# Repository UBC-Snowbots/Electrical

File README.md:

# UBC Rover Electrical Subteam Repository

Work is organized year by year (For now?)

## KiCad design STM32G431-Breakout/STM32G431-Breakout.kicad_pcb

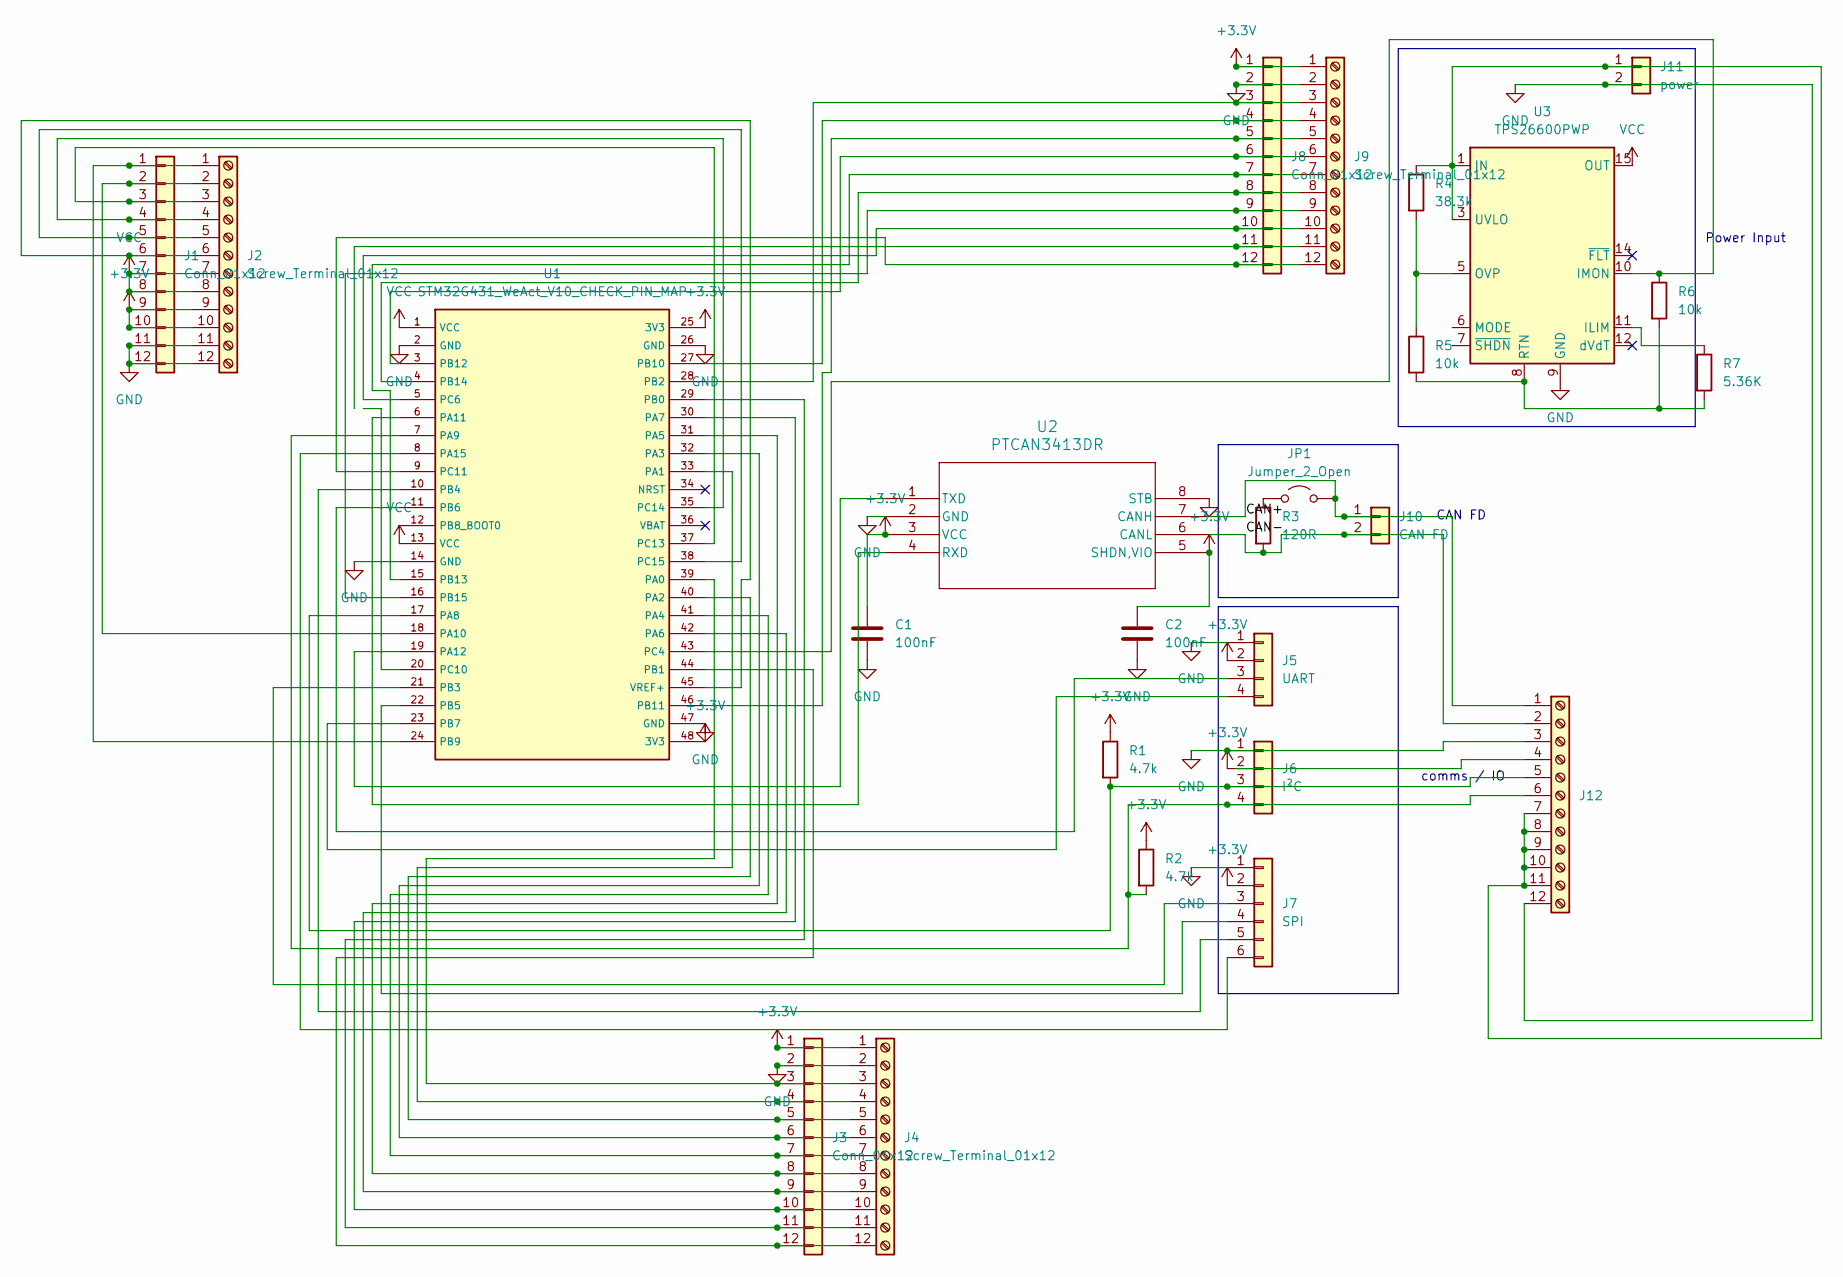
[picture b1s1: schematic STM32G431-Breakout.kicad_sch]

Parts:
C1, C2: 100nF; C_0603_1608Metric
J1, J3, J8: Conn_01x12; PinSocket_1x12_P2.54mm_Vertical
J2, J4, J9, J12: Screw_Terminal_01x12; TerminalBlock_MaiXu_MX126-5.0-12P_1x12_P5.00mm
J5: UART; JST_PH_S4B-PH-K_1x04_P2.00mm_Horizontal
J6: I²C; JST_PH_S4B-PH-K_1x04_P2.00mm_Horizontal
J7: SPI; JST_PH_S6B-PH-K_1x06_P2.00mm_Horizontal
J10: CAN FD; JST_PH_S2B-PH-K_1x02_P2.00mm_Horizontal
J11: power; JST_PH_S2B-PH-K_1x02_P2.00mm_Horizontal
JP1: Jumper_2_Open; PinHeader_1x02_P2.54mm_Vertical
R1, R2: 4.7k; R_0603_1608Metric
R3: 120R; R_0603_1608Metric
R4: 38.3k; R_0603_1608Metric
R5, R6: 10k; R_0603_1608Metric
R7: 5.36K; R_0603_1608Metric
U1: STM32G431_WeAct_V10_CHECK_PIN_MAP; stm32g431
U2: PTCAN3413DR; SOIC8_D_TEX
U3: TPS26600PWP; HTSSOP-16-1EP_4.4x5mm_P0.65mm_EP3.4x5mm_Mask2.66x2.46mm_The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

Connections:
+3.3V: C1.1, C2.1, J1.9, J1.10, J2.9, J2.10, J3.1, J4.1, J5.2, J6.2, J7.2, J8.1, J9.1, R1.1, R2.1, U1.25 (3V3), U1.48 (3V3), U2.3 (VCC), U2.5 (SHDN,VIO)
/CAN+: J10.1, J12.1, JP1.2 (B), U2.7 (CANH)
/CAN-: J10.2, J12.2, R3.2, U2.6 (CANL)
GND: C1.2, C2.2, J1.11, J1.12, J2.11, J2.12, J3.2, J4.2, J5.1, J6.1, J7.1, J8.2, J9.2, J11.2, J12.3, J12.12, U1.2 (GND), U1.14 (GND), U1.26 (GND), U1.47 (GND), U2.2 (GND), U2.8 (STB), U3.9 (GND)
unnamed: J1.1, J2.1, U1.24 (PB9)
unnamed: J1.2, J2.2, U1.18 (PA10)
unnamed: J1.3, J2.3, U1.37 (PC13)
unnamed: J1.4, J2.4, U1.35 (PC14)
unnamed: J1.5, J2.5, U1.38 (PC15)
unnamed: J1.6, J2.6, U1.45 (VREF+)
unnamed: J3.3, J4.3, U1.39 (PA0)
unnamed: J3.4, J4.4, U1.33 (PA1)
unnamed: J3.5, J4.5, U1.40 (PA2)
unnamed: J3.6, J4.6, U1.32 (PA3)
unnamed: J3.7, J4.7, U1.41 (PA4)
unnamed: J3.8, J4.8, U1.31 (PA5)
unnamed: J3.9, J4.9, U1.42 (PA6)
unnamed: J3.10, J4.10, U1.30 (PA7)
unnamed: J3.11, J4.11, U1.29 (PB0)
unnamed: J3.12, J4.12, U1.44 (PB1)
unnamed: J5.3, U1.11 (PB6)
unnamed: J5.4, U1.23 (PB7)
unnamed: J7.3, U1.21 (PB3)
unnamed: J7.4, U1.22 (PB5)
unnamed: J7.5, U1.10 (PB4)
unnamed: J7.6, U1.8 (PA15)
unnamed: J8.3, J9.3, U1.28 (PB2)
unnamed: J8.4, J9.4, U1.27 (PB10)
unnamed: J8.5, J9.5, U1.46 (PB11)
unnamed: J8.6, J9.6, U1.3 (PB12)
unnamed: J8.7, J9.7, U1.15 (PB13)
unnamed: J8.8, J9.8, U1.4 (PB14)
unnamed: J8.9, J9.9, U1.16 (PB15)
unnamed: J8.10, J9.10, U1.5 (PC6)
unnamed: J8.11, J9.11
unnamed: J8.12, J9.12, U1.9 (PC11)
unnamed: J11.1, J12.7, J12.8, J12.9, J12.10, J12.11, R4.1, U3.1 (IN), U3.2 (IN), U3.3 (UVLO)
unnamed: J6.3, J12.5, R1.2, U1.17 (PA8)
unnamed: J6.4, J12.6, R2.2, U1.7 (PA9)
unnamed: JP1.1 (A), R3.1
unnamed: R5.2, R6.2, R7.2, U3.8 (RTN), U3.17 (RTN)
unnamed: U1.6 (PA11), U2.4 (RXD)
unnamed: U1.19 (PA12), U2.1 (TXD)
unnamed: R6.1, U1.43 (PC4), U3.10 (IMON)
unnamed: R7.1, U3.11 (ILIM)
unnamed: R4.2, R5.1, U3.5 (OVP)
VCC: J1.7, J1.8, J2.7, J2.8, U1.1 (VCC), U1.13 (VCC), U3.15 (OUT), U3.16 (OUT)

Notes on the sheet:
Power Input
comms / IO
CAN FD

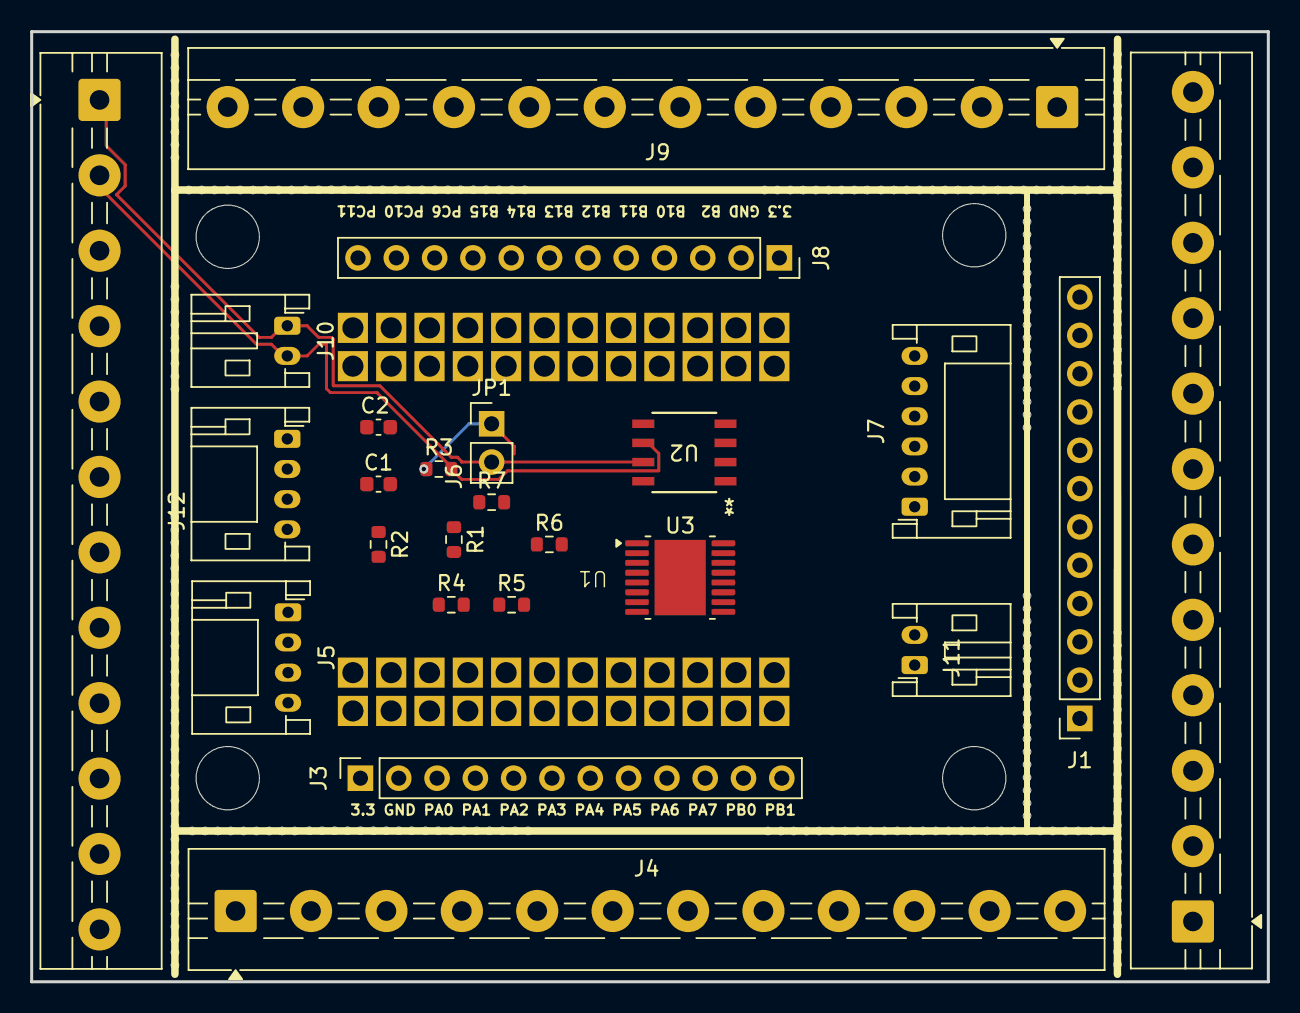
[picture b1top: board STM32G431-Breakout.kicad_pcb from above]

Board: 2 copper layers, 82.0 x 63.0 mm, 25 parts (0 on the bottom side), 47 nets.

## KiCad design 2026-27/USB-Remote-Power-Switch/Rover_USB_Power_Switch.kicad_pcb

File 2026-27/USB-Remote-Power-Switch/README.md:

# Rover USB 3.0 Remote Power Switch

USB 3.0 Type-A male-to-female pass-through PCB
with GPIO-controlled VBUS power switching.

## Requirements
- USB 3.0 (5 Gbps)
- USB-A male input and female output
- 500-900 mA target load current
- 3.3V / 5V GPIO control
- HIGH = Power OFF
- LOW or floating = Power ON

## Status
Work in progress — schematic and PCB under development.

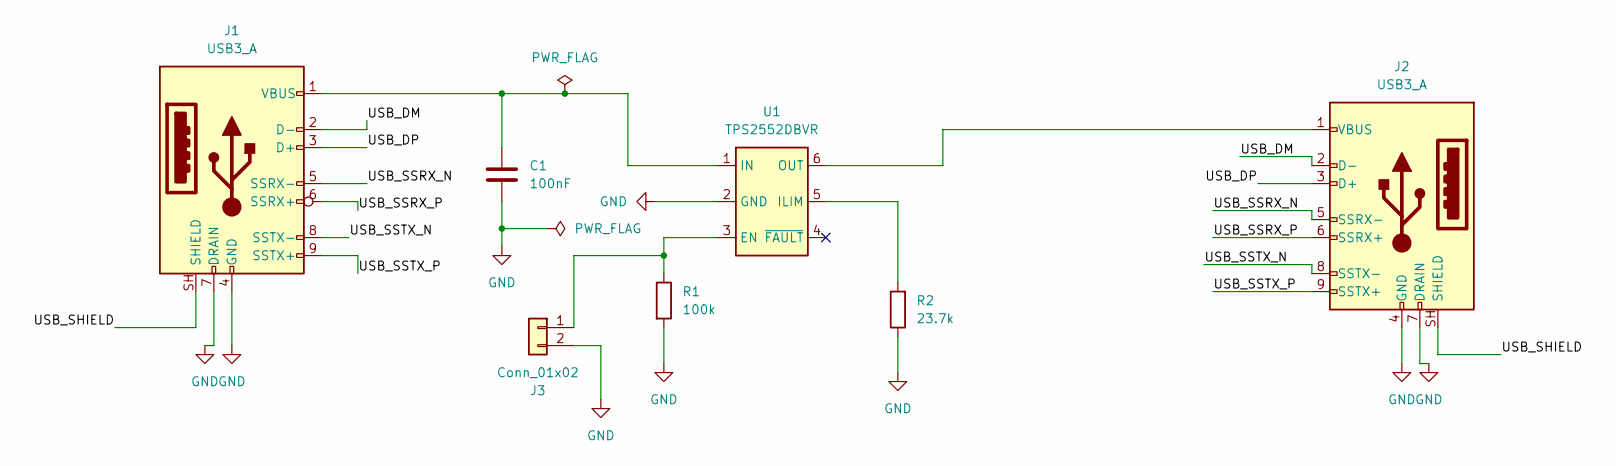
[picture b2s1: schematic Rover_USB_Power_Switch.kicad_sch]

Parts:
C1: 100nF; C_0603_1608Metric
J1: USB3_A; USB3_A_Plug_Wuerth_692112030100_Horizontal
J2: USB3_A; USB3_A_Receptacle_Wuerth_692122030100
J3: Conn_01x02; PinHeader_1x02_P2.54mm_Vertical
R1: 100k; R_0603_1608Metric
R2: 23.7k; R_0603_1608Metric
U1: TPS2552DBVR; SOT-23-6

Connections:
/USB_DM: J1.2 (D-), J2.2 (D-)
/USB_DP: J1.3 (D+), J2.3 (D+)
/USB_SHIELD: J1.SH (SHIELD), J2.SH (SHIELD)
/USB_SSRX_N: J1.5 (SSRX-), J2.5 (SSRX-)
/USB_SSRX_P: J1.6 (SSRX+), J2.6 (SSRX+)
/USB_SSTX_N: J1.8 (SSTX-), J2.8 (SSTX-)
/USB_SSTX_P: J1.9 (SSTX+), J2.9 (SSTX+)
GND: C1.2, J1.4 (GND), J1.7 (DRAIN), J2.4 (GND), J2.7 (DRAIN), J3.2, R1.2, R2.1, U1.2 (GND)
unnamed: C1.1, J1.1 (VBUS), U1.1 (IN)
unnamed: J2.1 (VBUS), U1.6 (OUT)
unnamed: J3.1, R1.1, U1.3 (EN)
unnamed: R2.2, U1.5 (ILIM)

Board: 2 copper layers, 7 parts (0 on the bottom side), 12 nets, no tracks yet.

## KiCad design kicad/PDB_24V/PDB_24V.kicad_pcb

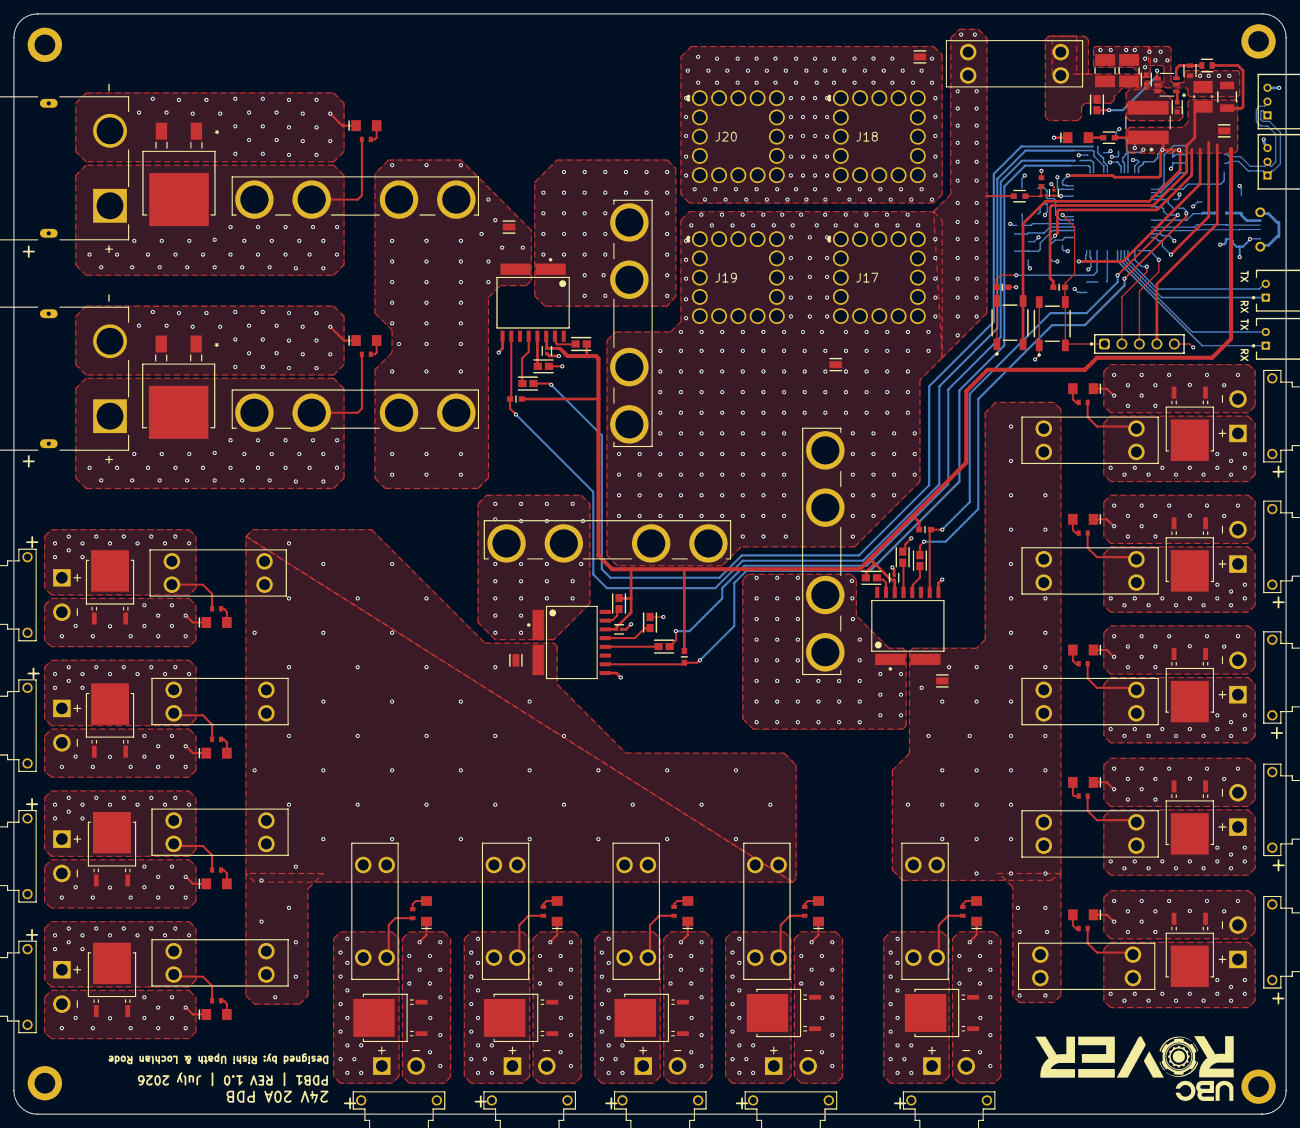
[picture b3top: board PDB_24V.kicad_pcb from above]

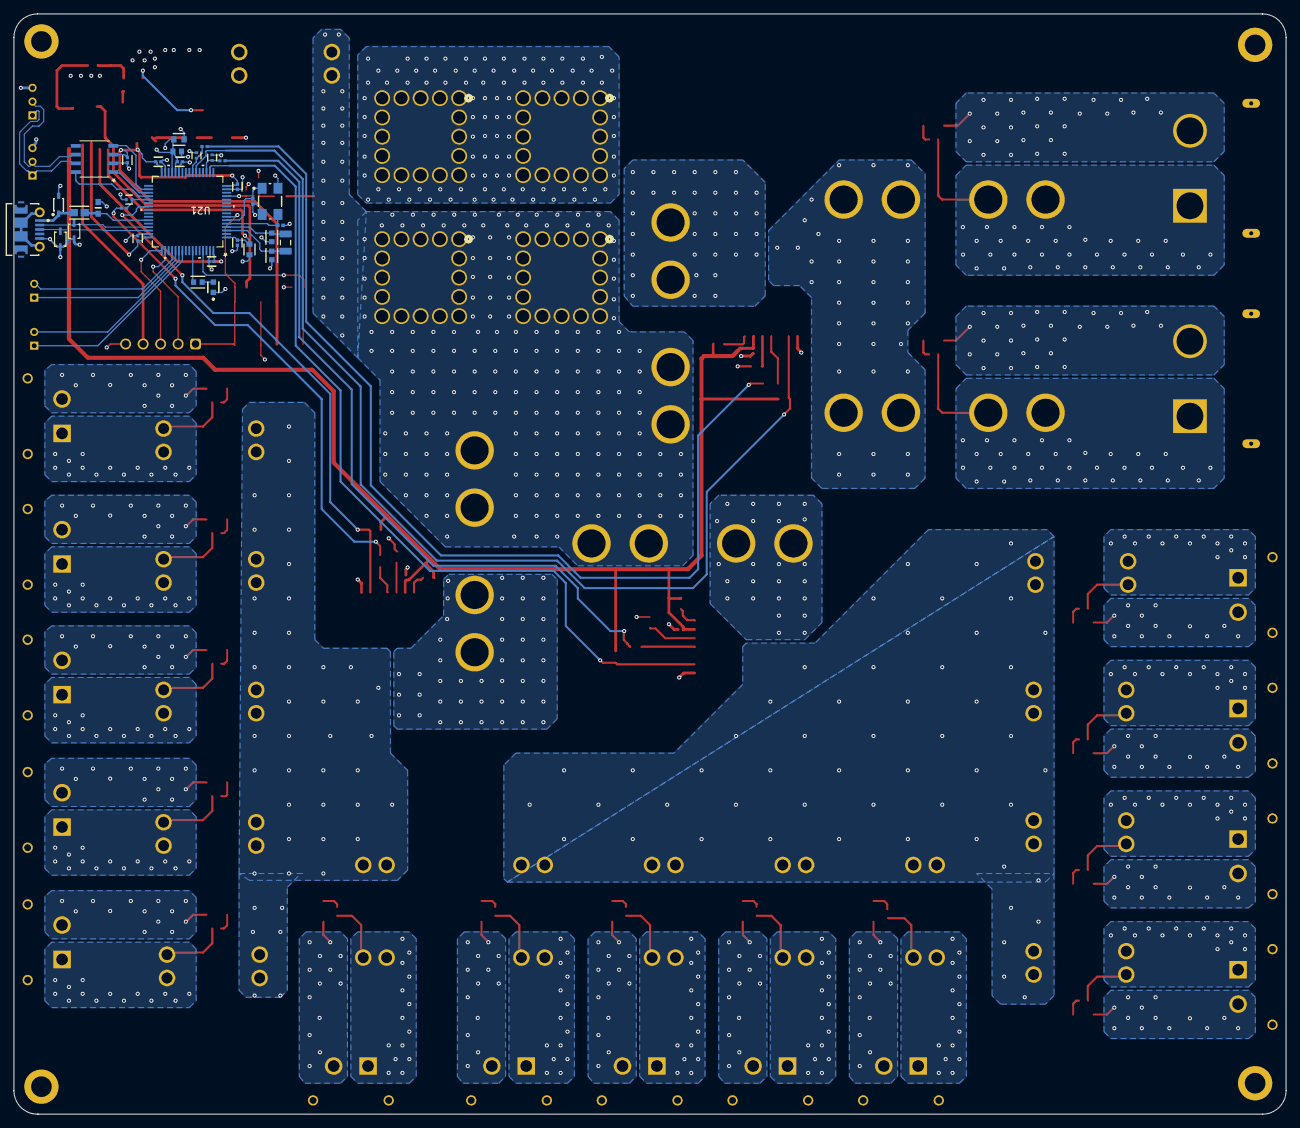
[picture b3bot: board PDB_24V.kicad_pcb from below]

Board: 4 copper layers, 185.0 x 160.0 mm, 170 parts (32 on the bottom side), 90 nets.

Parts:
C1, C4: CGA3E3X8R1H104K080AB; FP-CGA3E-0_3-0_1-MFG
C2, C3: 12105C475KAT2A; FP-1210-L_3_3_0_4-W_2_5_0-IPC_A
C5: UMK325BJ106MM-T; TAYO-C1210-2_M
C6: GRM32ER61E226KE15L; FP-GRM32-MFG
C7, C8, C9, C10, C12, C13, C14, C15, C16, C23: CL05B104KA5NNNC; FP-CL830-IPC_C
C11: GRM188R61E475KE11D; FP-GRM188-0_15-MFG
C17, C18: GRM1555C1H180JA01D; CAPC1005X55X25LL05T10
C19, C20: CL10C060DB8NNNC; FP-CL10-IPC_C
C21: CC0603KRX7R7BB105; FP-CC0603-DA-MFG
C22: GCM188R71H103KA37D; CAPC1608X90X35LL10T15
C24, C25, C26, C27: GRM1555C1H102JA01D; FP-GRM155-0_05-MFG
D1, D2, D3, D4, D5, D6, D7, D8, D9, D10, D11, D12, D13, D14, D15, D16, D17: 150120VS75000; WL-SMCW_1206_150120xx75000
D18: LTST-C191KGKT; FP-LTST-C191KGKT-MFG
D19: TSD05DYFR; FP-DYF0002A-MFG
F1, F5, F6, F7, F10, F11, F12, F13, F14, F15, F16, F17, F18, F19, F20: 3557-2; FUSE_3557-2
F2, F3, F4, F8, F9: 3555-2; FUSE_3555-2
J1, J2, J3, J6, J7, J8, J9, J10, J11, J12, J13, J14, J15, J16: XT30PW-F; AMASS_XT30PW-F
J4, J5: XT90PW-F; AMASS_XT90PW-F
J17, J18, J19, J20: S93515; CONN16_S93515_WRE
J21, J22: S3B-PH-K-S(LF)(SN); FP-S3B-PH-K-S_LF_SN-MFG
J23: 1050170001; USB-MICRO-B_V
J24, J25, J26, J27, J28, J29: S2761-46R; FP-S2761-46R-MFG
L1: SRN6045-8R2Y; IND_BOURNS_SRN6045
P1, P2: S2B-PH-K-S(LF)(SN); JST-S2B-PH-K-S_V
P3: 61300511121
R1, R7, R8, R10, R30, R38, R39, R40, R41, R42, R43: RMCF0603ZT0R00; FP-RMCF0603-IPC_A
R2: AC0603FR-07130RL; FP-AC0603-MFG
R3: CRCW060369K8FKEB; FP-CRCW0603-e3-MFG
R4: RMCF0603FT22K1; FP-RMCF0603-MFG
R5, R6, R9, R28, R29, R31: RC0603FR-0710KL; FP-RC0603-0_55-MFG
R11, R12, R13, R14, R15, R16, R17, R18, R19, R20, R21, R22, R23, R24, R25, R26: RC0603FR-072K2L; RESC1608X55X25LL10T15
R27: CRGCQ0603J220R; FP-CRGCQ0603-IPC_C
R32, R33, R34, R36: RC0402FR-07150RL; RESC1005X40X25LL05T10
R35: AC0603FR-0718KL; FP-AC0603-MFG
R37: ERJ-3EKF2001V; RESC1608X55X30LL15T15
SW1, SW2: 8-1437565-1; FP-8-1437565-1-MFG
U1: LMR54410DBVR; SOT-23-6-DBV_TEX
U2, U3, U4: TMCS1123B1AQDVGR; DVG0010A-MFG
U5, U6, U7, U10, U11, U12, U13, U14, U15, U16, U17, U18, U19, U20: SDT30B100D1-13; TO252_DIO
U8, U9: V40DL45-M3I; SOT_45-M3I_VIS
U21: STM32G491RET6; LQFP64_10X10_STM
U22: TCAN3404DRQ1; SOIC8_D_TEX
U23, U24: D5V0L1B2WS-7; SOD323_DIO
Y1: ABM3C-16.000MHZ-D4Y-T; FP-ABM3C-MFG
Y2: ABS07-166-32.768KHZ-T; EPSON-FC-135_V

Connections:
3.3V: C5.2, C6.2, C7.2, C8.2, C9.2, C10.2, C11.2, C12.2, C13.2, C14.2, C15.2, C16.2, C21.2, C22.2, C23.2, J26.1, L1.1, P3.4, R2.1, R3.2, R5.2, R6.2, R9.2, R28.2, R40.1, R41.1, R43.1, SW1.3, SW1.4, U2.8, U3.8, U4.8, U21.1, U21.16, U21.28, U21.29, U21.32, U21.48, U21.64, U22.3
3V3_CB: C1.1, U1.1
3V3_EN: R1.2, U1.4
3V3_FB: R3.1, R4.1, U1.3
3V3_SW: C1.2, L1.2, U1.6
5V_UART_RX: P2.1, U21.55
5V_UART_TX: P2.2, U21.54
18V_12V_UART_RX: P1.1, U21.53
18V_12V_UART_TX: P1.2, U21.52
24V: F1.1_1, F1.1_2, F2.1_1, F2.1_2, F3.1_1, F3.1_2, F4.1_1, F4.1_2, J17.1, J17.2, J17.3, J17.4, J17.5, J17.6, J17.7, J17.8, J17.9, J17.10, J17.11, J17.12, J17.13, J17.14, J17.15, J17.16, J19.1, J19.2, J19.3, J19.4, J19.5, J19.6, J19.7, J19.8, J19.9, J19.10, J19.11, J19.12, J19.13, J19.14, J19.15, J19.16, J24.1, R35.2
24V_ARM1: F8.2_1, F8.2_2, J4.P, R14.2, U8.3
24V_ARM2: F9.2_1, F9.2_2, J5.P, R15.2, U9.3
24V_ARM_F: F2.2_1, F2.2_2, U2.1
24V_ARM_S: F8.1_1, F8.1_2, F9.1_1, F9.1_2, J28.1, U2.2
24V_BUCK: C2.1, C3.1, C4.2, F1.2_1, F1.2_2, R1.1, U1.5
24V_CHASSIS_F: F3.2_1, F3.2_2, U3.1
24V_CHASSIS_S: F5.1_1, F5.1_2, F6.1_1, F6.1_2, F7.1_1, F7.1_2, F10.1_1, F10.1_2, F11.1_1, F11.1_2, F12.1_1, F12.1_2, J27.1, U3.2
24V_LIGTHING: F14.2_1, F14.2_2, J10.P, R20.2, U14.3
24V_M0: F5.2_1, F5.2_2, J1.P, R11.2, U5.3
24V_M1: F6.2_1, F6.2_2, J2.P, R12.2, U6.3
24V_M2: F7.2_1, F7.2_2, J3.P, R13.2, U7.3
24V_M3: F10.2_1, F10.2_2, J6.P, R16.2, U10.3
24V_M4: F11.2_1, F11.2_2, J7.P, R17.2, U11.3
24V_M5: F12.2_1, F12.2_2, J8.P, R18.2, U12.3
24V_MISC_F: F4.2_1, F4.2_2, U4.1
24V_MISC_S: F13.1_1, F13.1_2, F14.1_1, F14.1_2, F15.1_1, F15.1_2, F16.1_1, F16.1_2, F17.1_1, F17.1_2, F18.1_1, F18.1_2, F19.1_1, F19.1_2, F20.1_1, F20.1_2, J29.1, U4.2
24V_PoE: F18.2_1, F18.2_2, J14.P, R24.2, U18.3
24V_SCIENCE: F13.2_1, F13.2_2, J9.P, R19.2, U13.3
24V_SPARE_1: F15.2_1, F15.2_2, J11.P, R21.2, U15.3
24V_SPARE_2: F16.2_1, F16.2_2, J12.P, R22.2, U16.3
24V_SPARE_3: F17.2_1, F17.2_2, J13.P, R23.2, U17.3
24V_SPARE_4: F19.2_1, F19.2_2, J15.P, R25.2, U19.3
24V_SPARE_5: F20.2_1, F20.2_2, J16.P, R26.2, U20.3
ARM_ALERT: R5.1, U2.4, U21.22
ARM_SENSE: R7.2, R34.1
ARM_SENSE_IN: C26.2, R34.2, U21.23
B3.3V_LED: D1.2, R2.2
B24_Voltage: C27.2, R36.2, U21.13
B24_Voltage_In: R35.1, R36.1, R37.2
CAN_N: J21.2, J22.2, U22.6
CAN_P: J21.1, J22.1, U22.7
CAN_RX: U21.34, U22.4
CAN_STB: U21.36, U22.8
CAN_TX: U21.35, U22.1
CHASSIS_ALERT: R6.1, U3.4, U21.39
CHASSIS_SENSE: R8.2, R33.1
CHASSIS_SENSE_IN: C25.2, R33.2, U21.37
GND: C2.2, C3.2, C4.1, C5.1, C6.1, C7.1, C8.1, C9.1, C10.1, C11.1, C12.1, C13.1, C14.1, C15.1, C16.1, C17.1, C18.1, C19.1, C20.1, C21.1, C22.1, C23.1, C24.1, C25.1, C26.1, C27.1, D1.1, D2.1, D3.1, D4.1, D5.1, D6.1, D7.1, D8.1, D9.1, D10.1, D11.1, D12.1, D13.1, D14.1, D15.1, D16.1, D17.1, D18.1, D19.2, J1.N, J2.N, J3.N, J4.N, J5.N, J6.N, J7.N, J8.N, J9.N, J10.N, J11.N, J12.N, J13.N, J14.N, J15.N, J16.N, J18.1, J18.2, J18.3, J18.4, J18.5, J18.6, J18.7, J18.8, J18.9, J18.10, J18.11, J18.12, J18.13, J18.14, J18.15, J18.16, J20.1, J20.2, J20.3, J20.4, J20.5, J20.6, J20.7, J20.8, J20.9, J20.10, J20.11, J20.12, J20.13, J20.14, J20.15, J20.16, J21.3, J22.3, J23.5, J23.6, J23.7, J23.8, J23.9, J23.10, J23.11, J25.1, P3.5, R4.2, R29.1, R31.1, R37.1, R38.2, R39.2, R42.2, SW2.1, SW2.2, U1.2, U2.3, U3.3, U4.3, U5.1, U5.2, U6.1, U6.2, U7.1, U7.2, U8.1, U8.2, U9.1, U9.2, U10.1, U10.2, U11.1, U11.2, U12.1, U12.2, U13.1, U13.2, U14.1, U14.2, U15.1, U15.2, U16.1, U16.2, U17.1, U17.2, U18.1, U18.2, U19.1, U19.2, U20.1, U20.2, U21.15, U21.27, U21.31, U21.47, U21.63, U22.2, U23.2, U24.2, Y1.2, Y1.4
HSE_OSC_IN: C18.2, U21.5, Y1.3
HSE_OSC_OUT: C17.2, U21.6, Y1.1
LED_DEBUG_1: D18.2, R27.1
LED_DEBUG_2: R27.2, U21.58
LSE_OSC_IN: C20.2, U21.3, Y2.2
LSE_OSC_OUT: C19.2, U21.4, Y2.1
MCU_BOOT0: R29.2, SW1.1, SW1.2, U21.61
MCU_NRST: P3.1, R28.1, SW2.3, SW2.4, U21.7
MISC_ALERT: R9.1, U4.4, U21.18
MISC_SENSE: R10.2, R32.1
MISC_SENSE_IN: C24.2, R32.2, U21.19
NetD2_2: D2.2, R11.1
NetD3_2: D3.2, R12.1
NetD4_2: D4.2, R13.1
NetD5_2: D5.2, R14.1
NetD6_2: D6.2, R15.1
NetD7_2: D7.2, R16.1
NetD8_2: D8.2, R17.1
NetD9_2: D9.2, R18.1
NetD10_2: D10.2, R19.1
NetD11_2: D11.2, R20.1
NetD12_2: D12.2, R21.1
NetD13_2: D13.2, R22.1
NetD14_2: D14.2, R23.1
NetD15_2: D15.2, R24.1
NetD16_2: D16.2, R25.1
NetD17_2: D17.2, R26.1
NetR7_1: R7.1, U2.6
NetR8_1: R8.1, U3.6
NetR10_1: R10.1, U4.6
NetR38_1: R38.1, U2.7
NetR39_1: R39.1, U3.7
NetR40_2: R40.2, U2.9
NetR41_2: R41.2, U3.9
NetR42_1: R42.1, U4.7
NetR43_2: R43.2, U4.9
SWD_SWCLK: P3.2, U21.50
SWD_SWDIO: P3.3, U21.49
USB_D_N: J23.2, U21.45, U23.1
USB_D_P: J23.3, U21.46, U24.1
VBUS: D19.1, J23.1, R30.2
VBUS_SENSE: R30.1, R31.2, U21.43

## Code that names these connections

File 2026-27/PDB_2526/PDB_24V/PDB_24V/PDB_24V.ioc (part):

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Mcu.Name=STM32G491R(C-E)Tx
Mcu.Package=LQFP64
Mcu.UserName=STM32G491RETx
PA1.GPIOParameters=GPIO_Label
PA1.GPIO_Label=SENSE_24V
PA1.Mode=IN2-Single-Ended
PA1.Signal=ADC1_IN2
PA11.Mode=Device
PA11.Signal=USB_DM
PA12.Mode=Device
PA12.Signal=USB_DP
PA13.Mode=Serial_Wire
PA13.Signal=SYS_JTMS-SWDIO
PA14.Mode=Serial_Wire
PA14.Signal=SYS_JTCK-SWCLK
PA4.GPIOParameters=GPIO_Label
PA4.GPIO_Label=MISC_ALERT
PA4.Signal=GPIO_Input
PA5.GPIOParameters=GPIO_Label
PA5.GPIO_Label=MISC_SENSE
PA5.Mode=IN13-Single-Ended
PA5.Signal=ADC2_IN13
PA9.GPIOParameters=GPIO_Label
PA9.GPIO_Label=VBUS_SENSE
PA9.Signal=GPIO_Input
PB12.Mode=FDCAN_Activate
PB12.Signal=FDCAN2_RX
PB13.Mode=FDCAN_Activate
PB13.Signal=FDCAN2_TX
PB14.GPIOParameters=GPIO_Label
PB14.GPIO_Label=CAN_STB
PB14.Signal=GPIO_Output
PB15.GPIOParameters=GPIO_Label
PB15.GPIO_Label=CHASSIS_SENSE
PB15.Mode=IN15-Single-Ended
PB15.Signal=ADC2_IN15
PB5.GPIOParameters=GPIO_Label
PB5.GPIO_Label=DEBUG_LED
PB5.Signal=GPIO_Output
PC10.Mode=Asynchronous
PC10.Signal=UART4_TX
PC11.Mode=Asynchronous
PC11.Signal=UART4_RX
PC12.Mode=Asynchronous
PC12.Signal=UART5_TX
PC14-OSC32_IN.Mode=LSE-External-Oscillator
PC14-OSC32_IN.Signal=RCC_OSC32_IN
PC15-OSC32_OUT.Mode=LSE-External-Oscillator
PC15-OSC32_OUT.Signal=RCC_OSC32_OUT
PC4.GPIOParameters=GPIO_Label
PC4.GPIO_Label=ARM_ALERT
PC4.Signal=GPIO_Input
PC5.GPIOParameters=GPIO_Label
PC5.GPIO_Label=ARM_SENSE
PC5.Mode=IN11-Single-Ended
PC5.Signal=ADC2_IN11
PC7.GPIOParameters=GPIO_Label
PC7.GPIO_Label=CHASSIS_ALERT
PC7.Signal=GPIO_Input
PD2.Mode=Asynchronous
PD2.Signal=UART5_RX
PF0-OSC_IN.Mode=HSE-External-Oscillator
PF0-OSC_IN.Signal=RCC_OSC_IN
PF1-OSC_OUT.Mode=HSE-External-Oscillator
PF1-OSC_OUT.Signal=RCC_OSC_OUT
RCC.HSE_VALUE=8000000
RCC.SYSCLKFreq_VALUE=16000000
board=custom

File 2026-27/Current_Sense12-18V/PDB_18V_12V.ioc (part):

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Mcu.Name=STM32G030K(6-8)Tx
Mcu.Package=LQFP32
Mcu.UserName=STM32G030K8Tx
PA13.Mode=Serial_Wire
PA13.Signal=SYS_SWDIO
PA14-BOOT0.Mode=Serial_Wire
PA14-BOOT0.Signal=SYS_SWCLK
PA2.GPIOParameters=GPIO_Label
PA2.GPIO_Label=B12_Voltage
PA2.Mode=IN2
PA2.Signal=ADC1_IN2
PA4.GPIOParameters=GPIO_Label
PA4.GPIO_Label=B12_Current
PA4.Mode=IN4
PA4.Signal=ADC1_IN4
PA6.GPIOParameters=GPIO_Label
PA6.GPIO_Label=PGOOD_12V
PA6.Signal=GPIO_Input
PA9.GPIOParameters=GPIO_Label
PA9.GPIO_Label=PGOOD_18V
PA9.Signal=GPIO_Input
PB0.GPIOParameters=GPIO_Label
PB0.GPIO_Label=B18_Voltage
PB0.Mode=IN8
PB0.Signal=ADC1_IN8
PB2.GPIOParameters=GPIO_Label
PB2.GPIO_Label=B18_Current
PB2.Mode=IN10
PB2.Signal=ADC1_IN10
PB3.GPIOParameters=GPIO_Label
PB3.GPIO_Label=DEBUG_LED
PB3.Signal=GPIO_Output
PB6.Mode=Asynchronous
PB6.Signal=USART1_TX
PB7.Mode=Asynchronous
PB7.Signal=USART1_RX
RCC.HSE_VALUE=8000000
RCC.SYSCLKFreq_VALUE=16000000
board=custom

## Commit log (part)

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2026-01-31 Initial C firmware for motor control using Nucleo.
2026-02-01 Added breaks and commands for L and R side control
2026-02-02 Added protections for invalid commands
2026-02-20 Added ctype.h for character validation
2026-02-21 Improved readability. Fixed critical logic errors.
2026-03-08 Improved readability
2026-03-15 Implemented debugging tests
2026-03-29 Added get_speed command in RPM
2026-03-29 Contains IOC and other setup files
2026-03-29 Removed code reduncancy. Updated README
